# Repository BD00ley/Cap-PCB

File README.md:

# Cap-PCB
So this project was an attempt (and I emphasize attempt) to create a PCB that would display various messages on my cap for graduation.
However, I didn't read the datasheet of the ATTiny85 properly nor did I go too deep into the PCF8574 I/O expanders and everything about this
board is wrong (I somehow got the SDA and SCL lines backwards and I used the I/O expanders for current sources rather than sinks.)
So while this project did fail, I did learn the importance of triple checking schematics and really thoroughly reading through datasheets
rather than just skimming them.

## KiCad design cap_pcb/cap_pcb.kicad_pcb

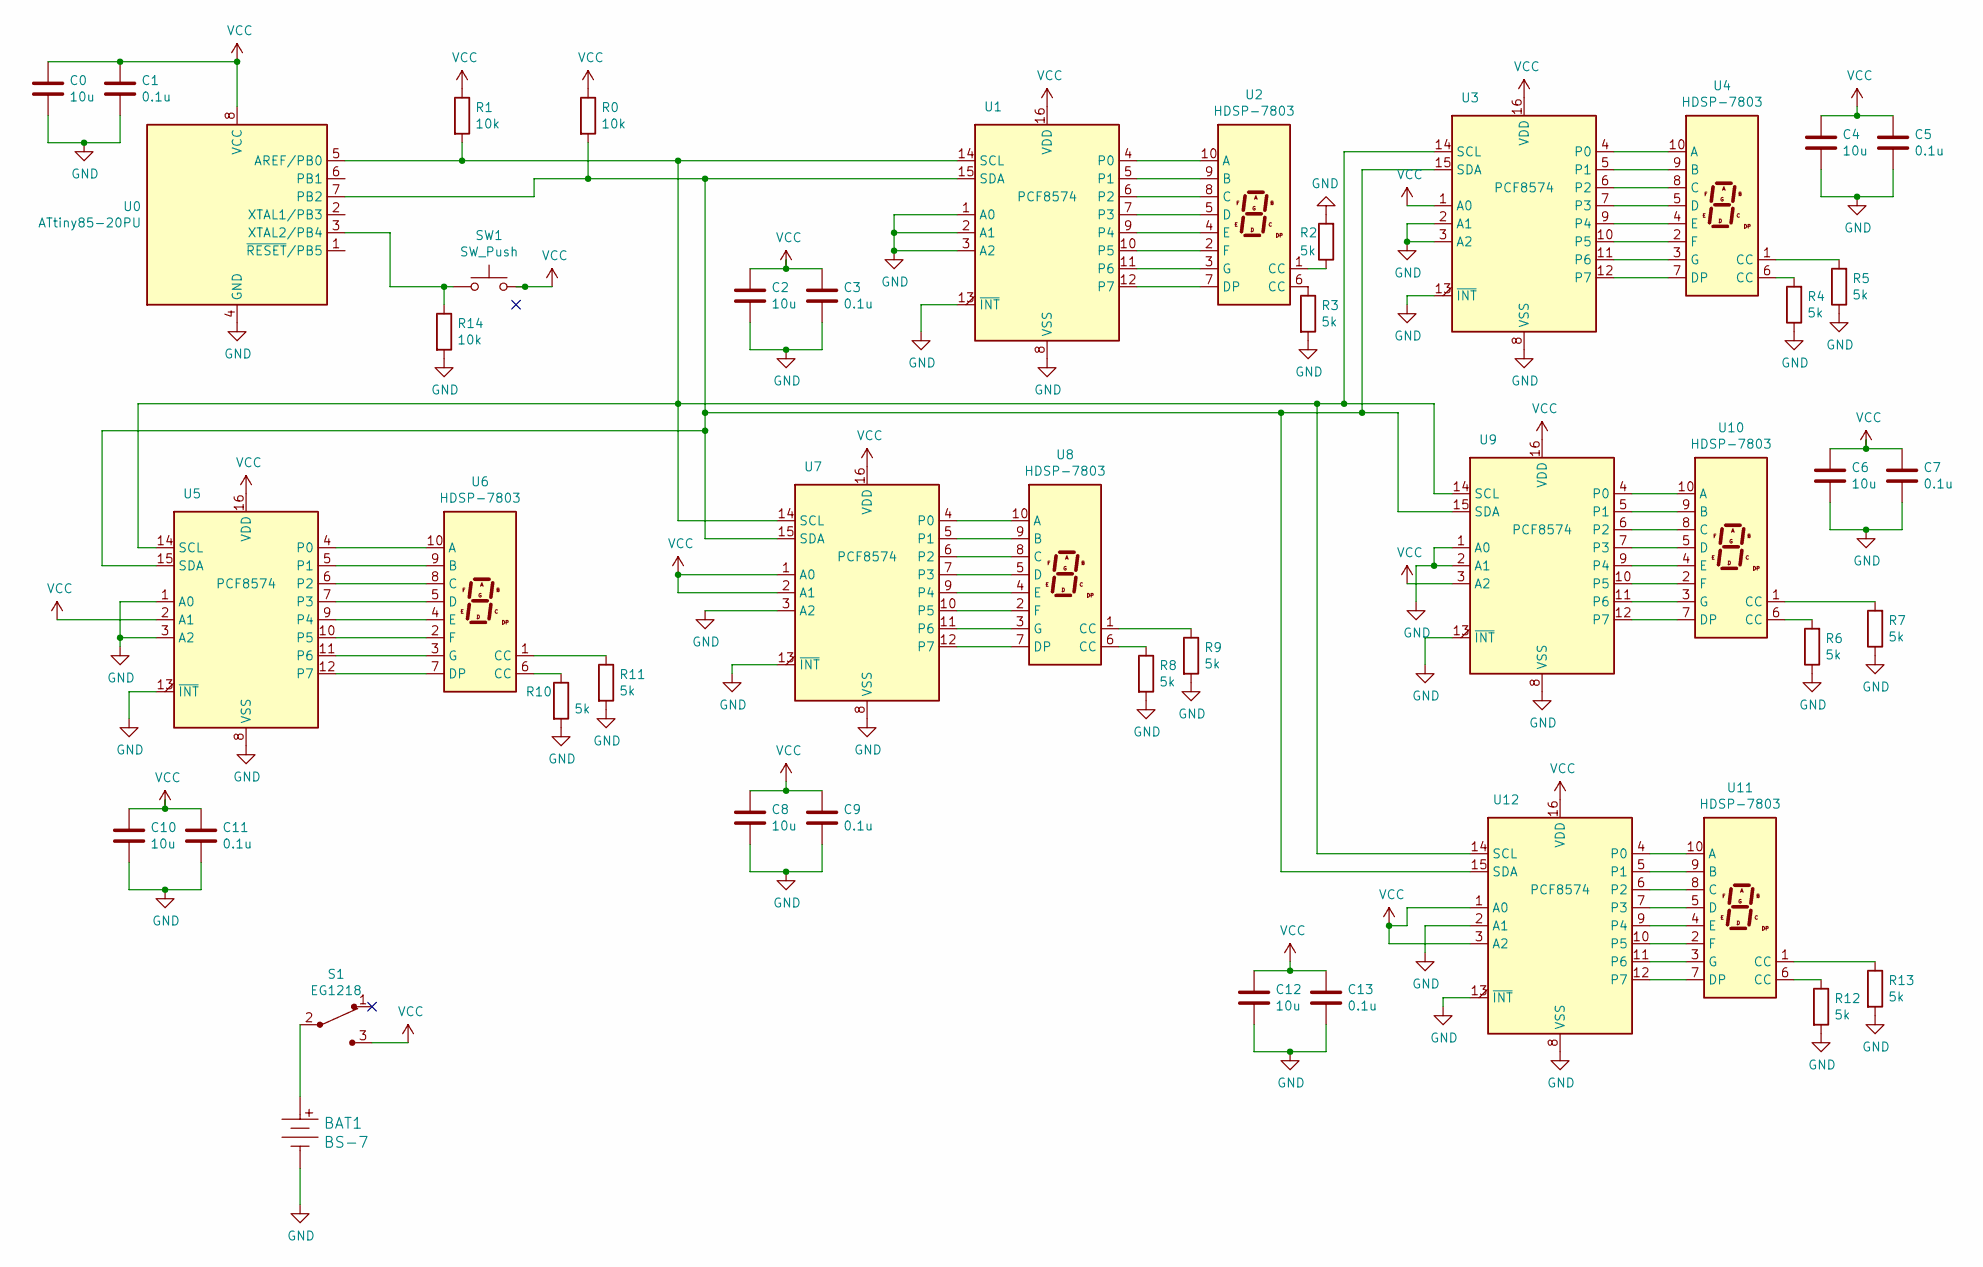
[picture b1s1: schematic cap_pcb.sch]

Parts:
BAT1: BS-7; Battery_Holder_Coin_2032_BS-7; MPN BS-7; Digi-Key_PN BS-7-ND
C0, C2, C4, C6, C8, C10, C12: 10u; C_1206_3216Metric_Pad1.33x1.80mm_HandSolder
C1, C3, C5, C7, C9, C11, C13: 0.1u; C_1206_3216Metric_Pad1.33x1.80mm_HandSolder
R0, R1, R14: 10k; R_Axial_DIN0411_L9.9mm_D3.6mm_P25.40mm_Horizontal
R2, R3, R4, R5, R6, R7, R8, R9, R10, R11, R12, R13: 5k; R_Axial_DIN0411_L9.9mm_D3.6mm_P25.40mm_Horizontal
S1: EG1218; Switch_Slide_11.6x4mm_EG1218; MPN EG1218; Digi-Key_PN EG1903-ND
SW1: SW_Push; SW_PUSH_6mm
U0: ATtiny85-20PU; DIP-8_W7.62mm_Socket
U1, U3, U5, U7, U9, U12: PCF8574; DIP-16_W7.62mm
U2, U4, U6, U8, U10, U11: HDSP-7803; HDSP-7801

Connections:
GND: BAT1.Neg, C0.2, C1.2, C2.2, C3.2, C4.2, C5.2, C6.2, C7.2, C8.2, C9.2, C10.2, C11.2, C12.2, C13.2, R2.2, R3.2, R4.1, R5.1, R6.1, R7.1, R8.2, R9.2, R10.2, R11.2, R12.2, R13.2, R14.2, U0.4 (GND), U1.1 (A0), U1.2 (A1), U1.3 (A2), U1.8 (VSS), U1.13 (~INT~), U3.2 (A1), U3.3 (A2), U3.8 (VSS), U3.13 (~INT~), U5.1 (A0), U5.3 (A2), U5.8 (VSS), U5.13 (~INT~), U7.3 (A2), U7.8 (VSS), U7.13 (~INT~), U9.1 (A0), U9.2 (A1), U9.8 (VSS), U9.13 (~INT~), U12.2 (A1), U12.8 (VSS), U12.13 (~INT~)
unnamed: BAT1.Pos, S1.2
unnamed: R0.2, U0.7 (PB2), U1.15 (SDA), U3.15 (SDA), U5.15 (SDA), U7.15 (SDA), U9.15 (SDA), U12.15 (SDA)
unnamed: R1.2, U0.5 (AREF/PB0), U1.14 (SCL), U3.14 (SCL), U5.14 (SCL), U7.14 (SCL), U9.14 (SCL), U12.14 (SCL)
unnamed: R2.1, U2.1 (CC)
unnamed: R3.1, U2.6 (CC)
unnamed: R4.2, U4.6 (CC)
unnamed: R5.2, U4.1 (CC)
unnamed: R6.2, U10.6 (CC)
unnamed: R7.2, U10.1 (CC)
unnamed: R8.1, U8.6 (CC)
unnamed: R9.1, U8.1 (CC)
unnamed: R10.1, U6.6 (CC)
unnamed: R11.1, U6.1 (CC)
unnamed: R12.1, U11.6 (CC)
unnamed: R13.1, U11.1 (CC)
unnamed: R14.1, SW1.1, U0.3 (XTAL2/PB4)
unnamed: U1.4 (P0), U2.10 (A)
unnamed: U1.5 (P1), U2.9 (B)
unnamed: U1.6 (P2), U2.8 (C)
unnamed: U1.7 (P3), U2.5 (D)
unnamed: U1.9 (P4), U2.4 (E)
unnamed: U1.10 (P5), U2.2 (F)
unnamed: U1.11 (P6), U2.3 (G)
unnamed: U1.12 (P7), U2.7 (DP)
unnamed: U3.4 (P0), U4.10 (A)
unnamed: U3.5 (P1), U4.9 (B)
unnamed: U3.6 (P2), U4.8 (C)
unnamed: U3.7 (P3), U4.5 (D)
unnamed: U3.9 (P4), U4.4 (E)
unnamed: U3.10 (P5), U4.2 (F)
unnamed: U3.11 (P6), U4.3 (G)
unnamed: U3.12 (P7), U4.7 (DP)
unnamed: U5.4 (P0), U6.10 (A)
unnamed: U5.5 (P1), U6.9 (B)
unnamed: U5.6 (P2), U6.8 (C)
unnamed: U5.7 (P3), U6.5 (D)
unnamed: U5.9 (P4), U6.4 (E)
unnamed: U5.10 (P5), U6.2 (F)
unnamed: U5.11 (P6), U6.3 (G)
unnamed: U5.12 (P7), U6.7 (DP)
unnamed: U7.4 (P0), U8.10 (A)
unnamed: U7.5 (P1), U8.9 (B)
unnamed: U7.6 (P2), U8.8 (C)
unnamed: U7.7 (P3), U8.5 (D)
unnamed: U7.9 (P4), U8.4 (E)
unnamed: U7.10 (P5), U8.2 (F)
unnamed: U7.11 (P6), U8.3 (G)
unnamed: U7.12 (P7), U8.7 (DP)
unnamed: U9.10 (P5), U10.2 (F)
unnamed: U9.11 (P6), U10.3 (G)
unnamed: U9.9 (P4), U10.4 (E)
unnamed: U9.7 (P3), U10.5 (D)
unnamed: U9.12 (P7), U10.7 (DP)
unnamed: U9.6 (P2), U10.8 (C)
unnamed: U9.5 (P1), U10.9 (B)
unnamed: U9.4 (P0), U10.10 (A)
unnamed: U11.2 (F), U12.10 (P5)
unnamed: U11.3 (G), U12.11 (P6)
unnamed: U11.4 (E), U12.9 (P4)
unnamed: U11.5 (D), U12.7 (P3)
unnamed: U11.7 (DP), U12.12 (P7)
unnamed: U11.8 (C), U12.6 (P2)
unnamed: U11.9 (B), U12.5 (P1)
unnamed: U11.10 (A), U12.4 (P0)
VCC: C0.1, C1.1, C2.1, C3.1, C4.1, C5.1, C6.1, C7.1, C8.1, C9.1, C10.1, C11.1, C12.1, C13.1, R0.1, R1.1, S1.3, SW1.2, U0.8 (VCC), U1.16 (VDD), U3.1 (A0), U3.16 (VDD), U5.2 (A1), U5.16 (VDD), U7.1 (A0), U7.2 (A1), U7.16 (VDD), U9.3 (A2), U9.16 (VDD), U12.1 (A0), U12.3 (A2), U12.16 (VDD)

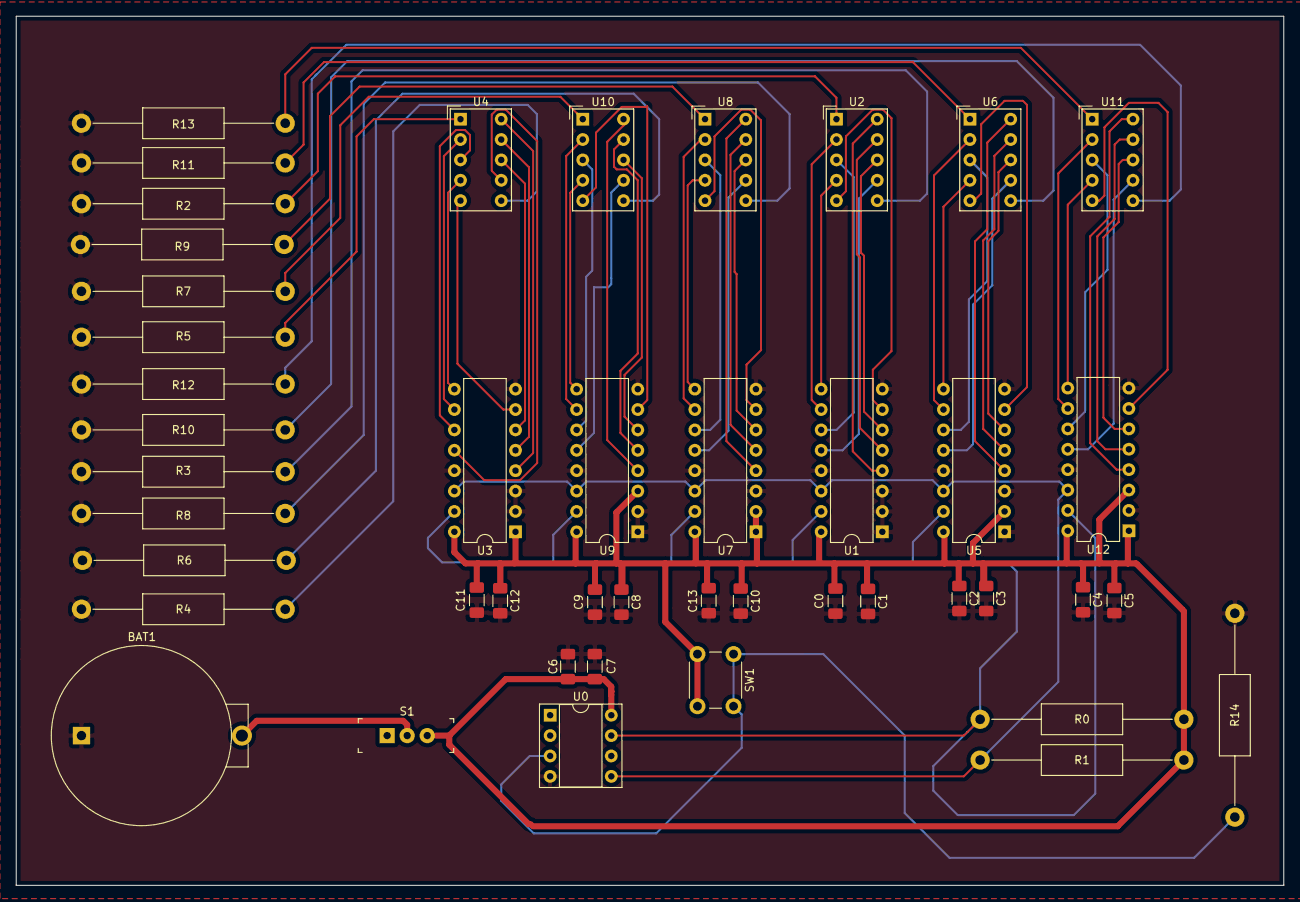
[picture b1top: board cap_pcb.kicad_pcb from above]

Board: 2 copper layers, 158.0 x 108.3 mm, 45 parts (0 on the bottom side), 66 nets.

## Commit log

2020-11-02 mostly finished pcb
2020-11-04 finalized pcb, added source folder
2020-11-05 skeleton files fleshed out some; added makefile
2020-11-16 fixed pcb to include proper ground (lol); added some src files for the attiny85
2022-05-21 this is nearly two years old, just updating this for my github profile
